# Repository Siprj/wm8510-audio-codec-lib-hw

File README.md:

wm8510-audio-codec-lib-hw
=========================

HW develepement desk and library for using wm8510

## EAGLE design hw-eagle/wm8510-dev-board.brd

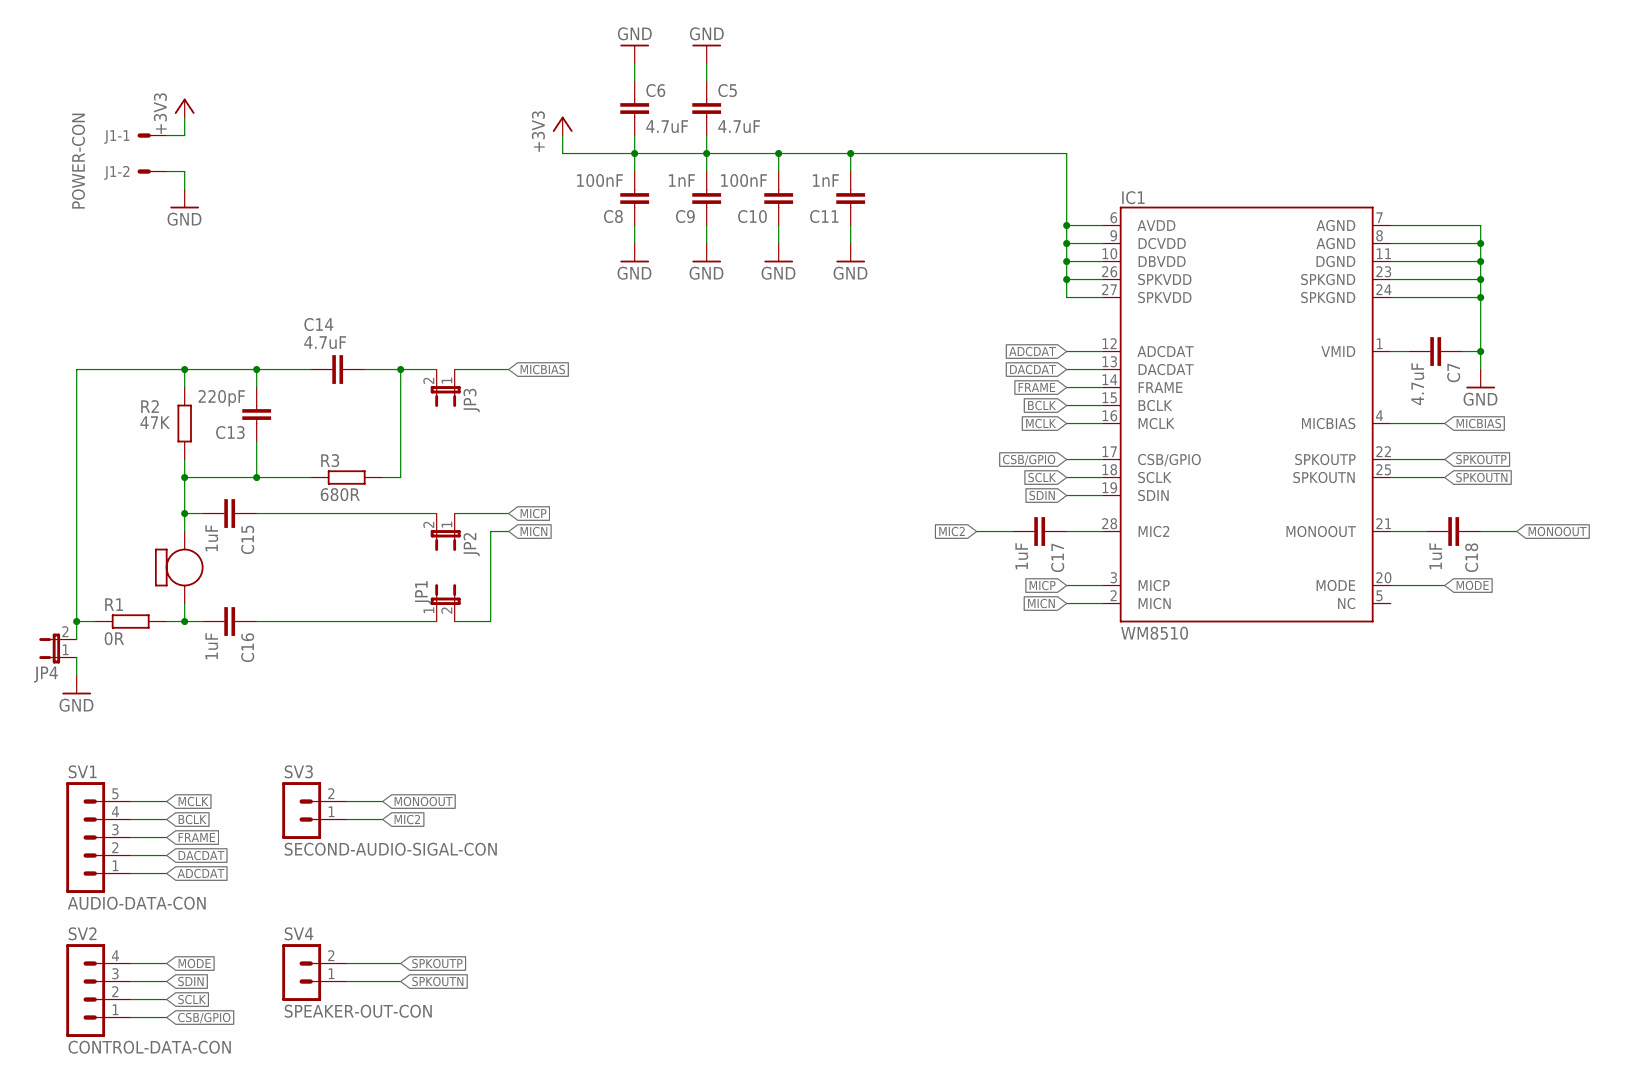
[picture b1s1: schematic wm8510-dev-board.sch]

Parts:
C5, C6, C7, C14: 4.7uF; C1206
C8, C10: 100nF; C1206
C9, C11: 1nF; C1206
C13: 220pF; C1206
C15, C16, C17, C18: 1uF; C1206
IC1: WM8510; SSOP28
J1: POWER-CON; 6410-02
JP1, JP2, JP3, JP4: JP1E; JP1
R1: 0R; R1206
R2: 47K; R1206
R3: 680R; R1206
SV1: AUDIO-DATA-CON; MA05-1
SV2: CONTROL-DATA-CON; MA04-1
SV3: SECOND-AUDIO-SIGAL-CON; MA03-1
SV4: SPEAKER-OUT-CON; MA03-1
U$2: ABM-707-RC

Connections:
+3V3: C5.2, C6.2, C8.2, C9.2, C10.2, C11.2, IC1.6 (AVDD), IC1.9 (DCVDD), IC1.10 (DBVDD), IC1.26 (SPKVDD), IC1.27 (SPKVDD), J1.1
ADCDAT: IC1.12 (ADCDAT), SV1.1
BCLK: IC1.15 (BCLK), SV1.4
CSB/GPIO: IC1.17 (CSB/GPIO), SV2.1
DACDAT: IC1.13 (DACDAT), SV1.2
FRAME: IC1.14 (FRAME), SV1.3
GND: C5.1, C6.1, C7.1, C8.1, C9.1, C10.1, C11.1, IC1.7 (AGND), IC1.8 (AGND), IC1.11 (DGND), IC1.23 (SPKGND), IC1.24 (SPKGND), J1.2, JP4.1
MCLK: IC1.16 (MCLK), SV1.5
MIC2: C17.2, SV3.1
MICBIAS: IC1.4 (MICBIAS), JP3.1
MICN: IC1.2 (MICN), JP1.2
MICP: IC1.3 (MICP), JP2.1
MODE: IC1.20 (MODE), SV2.4
MONOOUT: C18.1, SV3.2
unnamed: C7.2, IC1.1 (VMID)
unnamed: C13.1, C15.2, R2.2, R3.1, U$2.P$1
unnamed: C16.2, R1.2, U$2.P$2
unnamed: C14.1, JP3.2, R3.2
unnamed: C13.2, C14.2, JP4.2, R1.1, R2.1
unnamed: C16.1, JP1.1
unnamed: C15.1, JP2.2
unnamed: C17.1, IC1.28 (MIC2)
unnamed: C18.2, IC1.21 (MONOOUT)
SCLK: IC1.18 (SCLK), SV2.2
SDIN: IC1.19 (SDIN), SV2.3
SPKOUTN: IC1.25 (SPKOUTN), SV4.1
SPKOUTP: IC1.22 (SPKOUTP), SV4.2

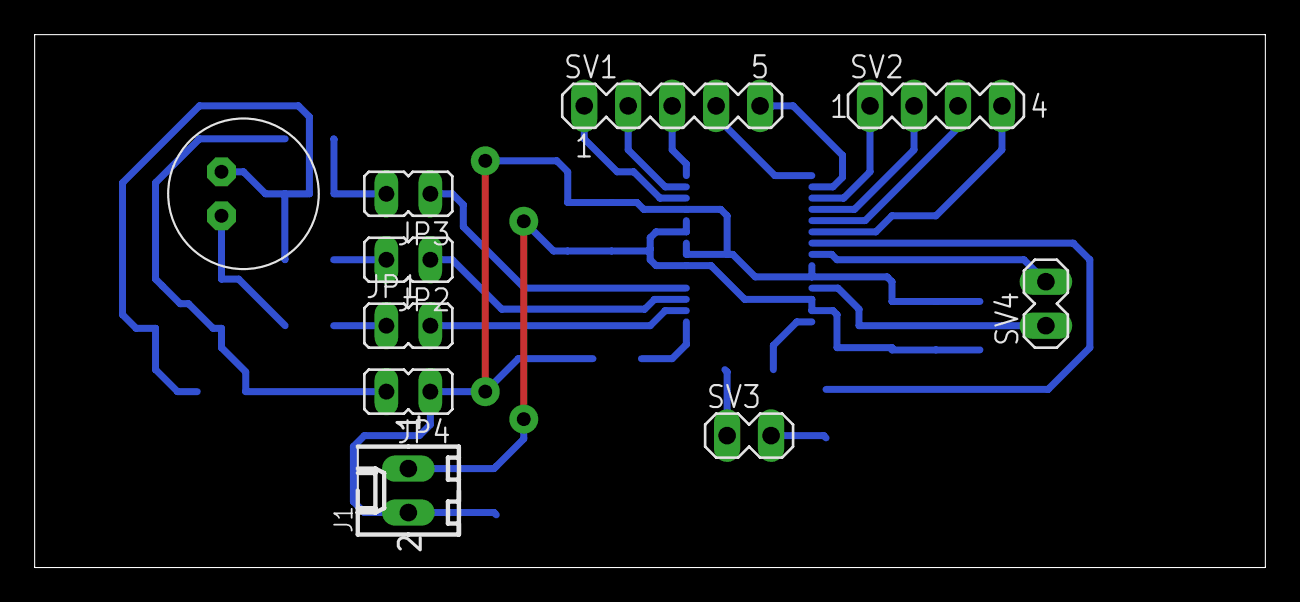
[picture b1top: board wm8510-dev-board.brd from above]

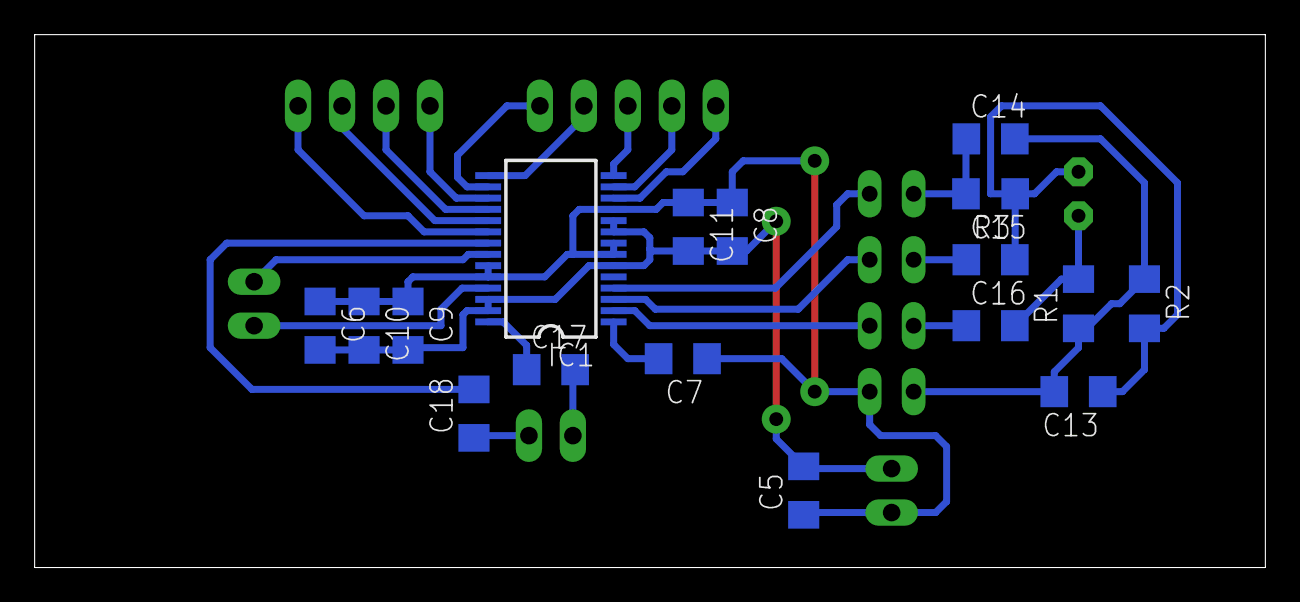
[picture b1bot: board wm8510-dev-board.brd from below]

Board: 2 copper layers, 71.1 x 30.8 mm, 27 parts (17 on the bottom side), 27 nets.

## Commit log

2014-08-12 Create schematic of development board.
    Create schematic of development board. Becouse of this I had to create
    part library with three parts (mic, pinhead with two points, wm8510
    part).
2014-08-12 Fix the values ​​of resistors and capacitors consisting microphone source .
2014-08-12 I created brd and I routed all routes.
